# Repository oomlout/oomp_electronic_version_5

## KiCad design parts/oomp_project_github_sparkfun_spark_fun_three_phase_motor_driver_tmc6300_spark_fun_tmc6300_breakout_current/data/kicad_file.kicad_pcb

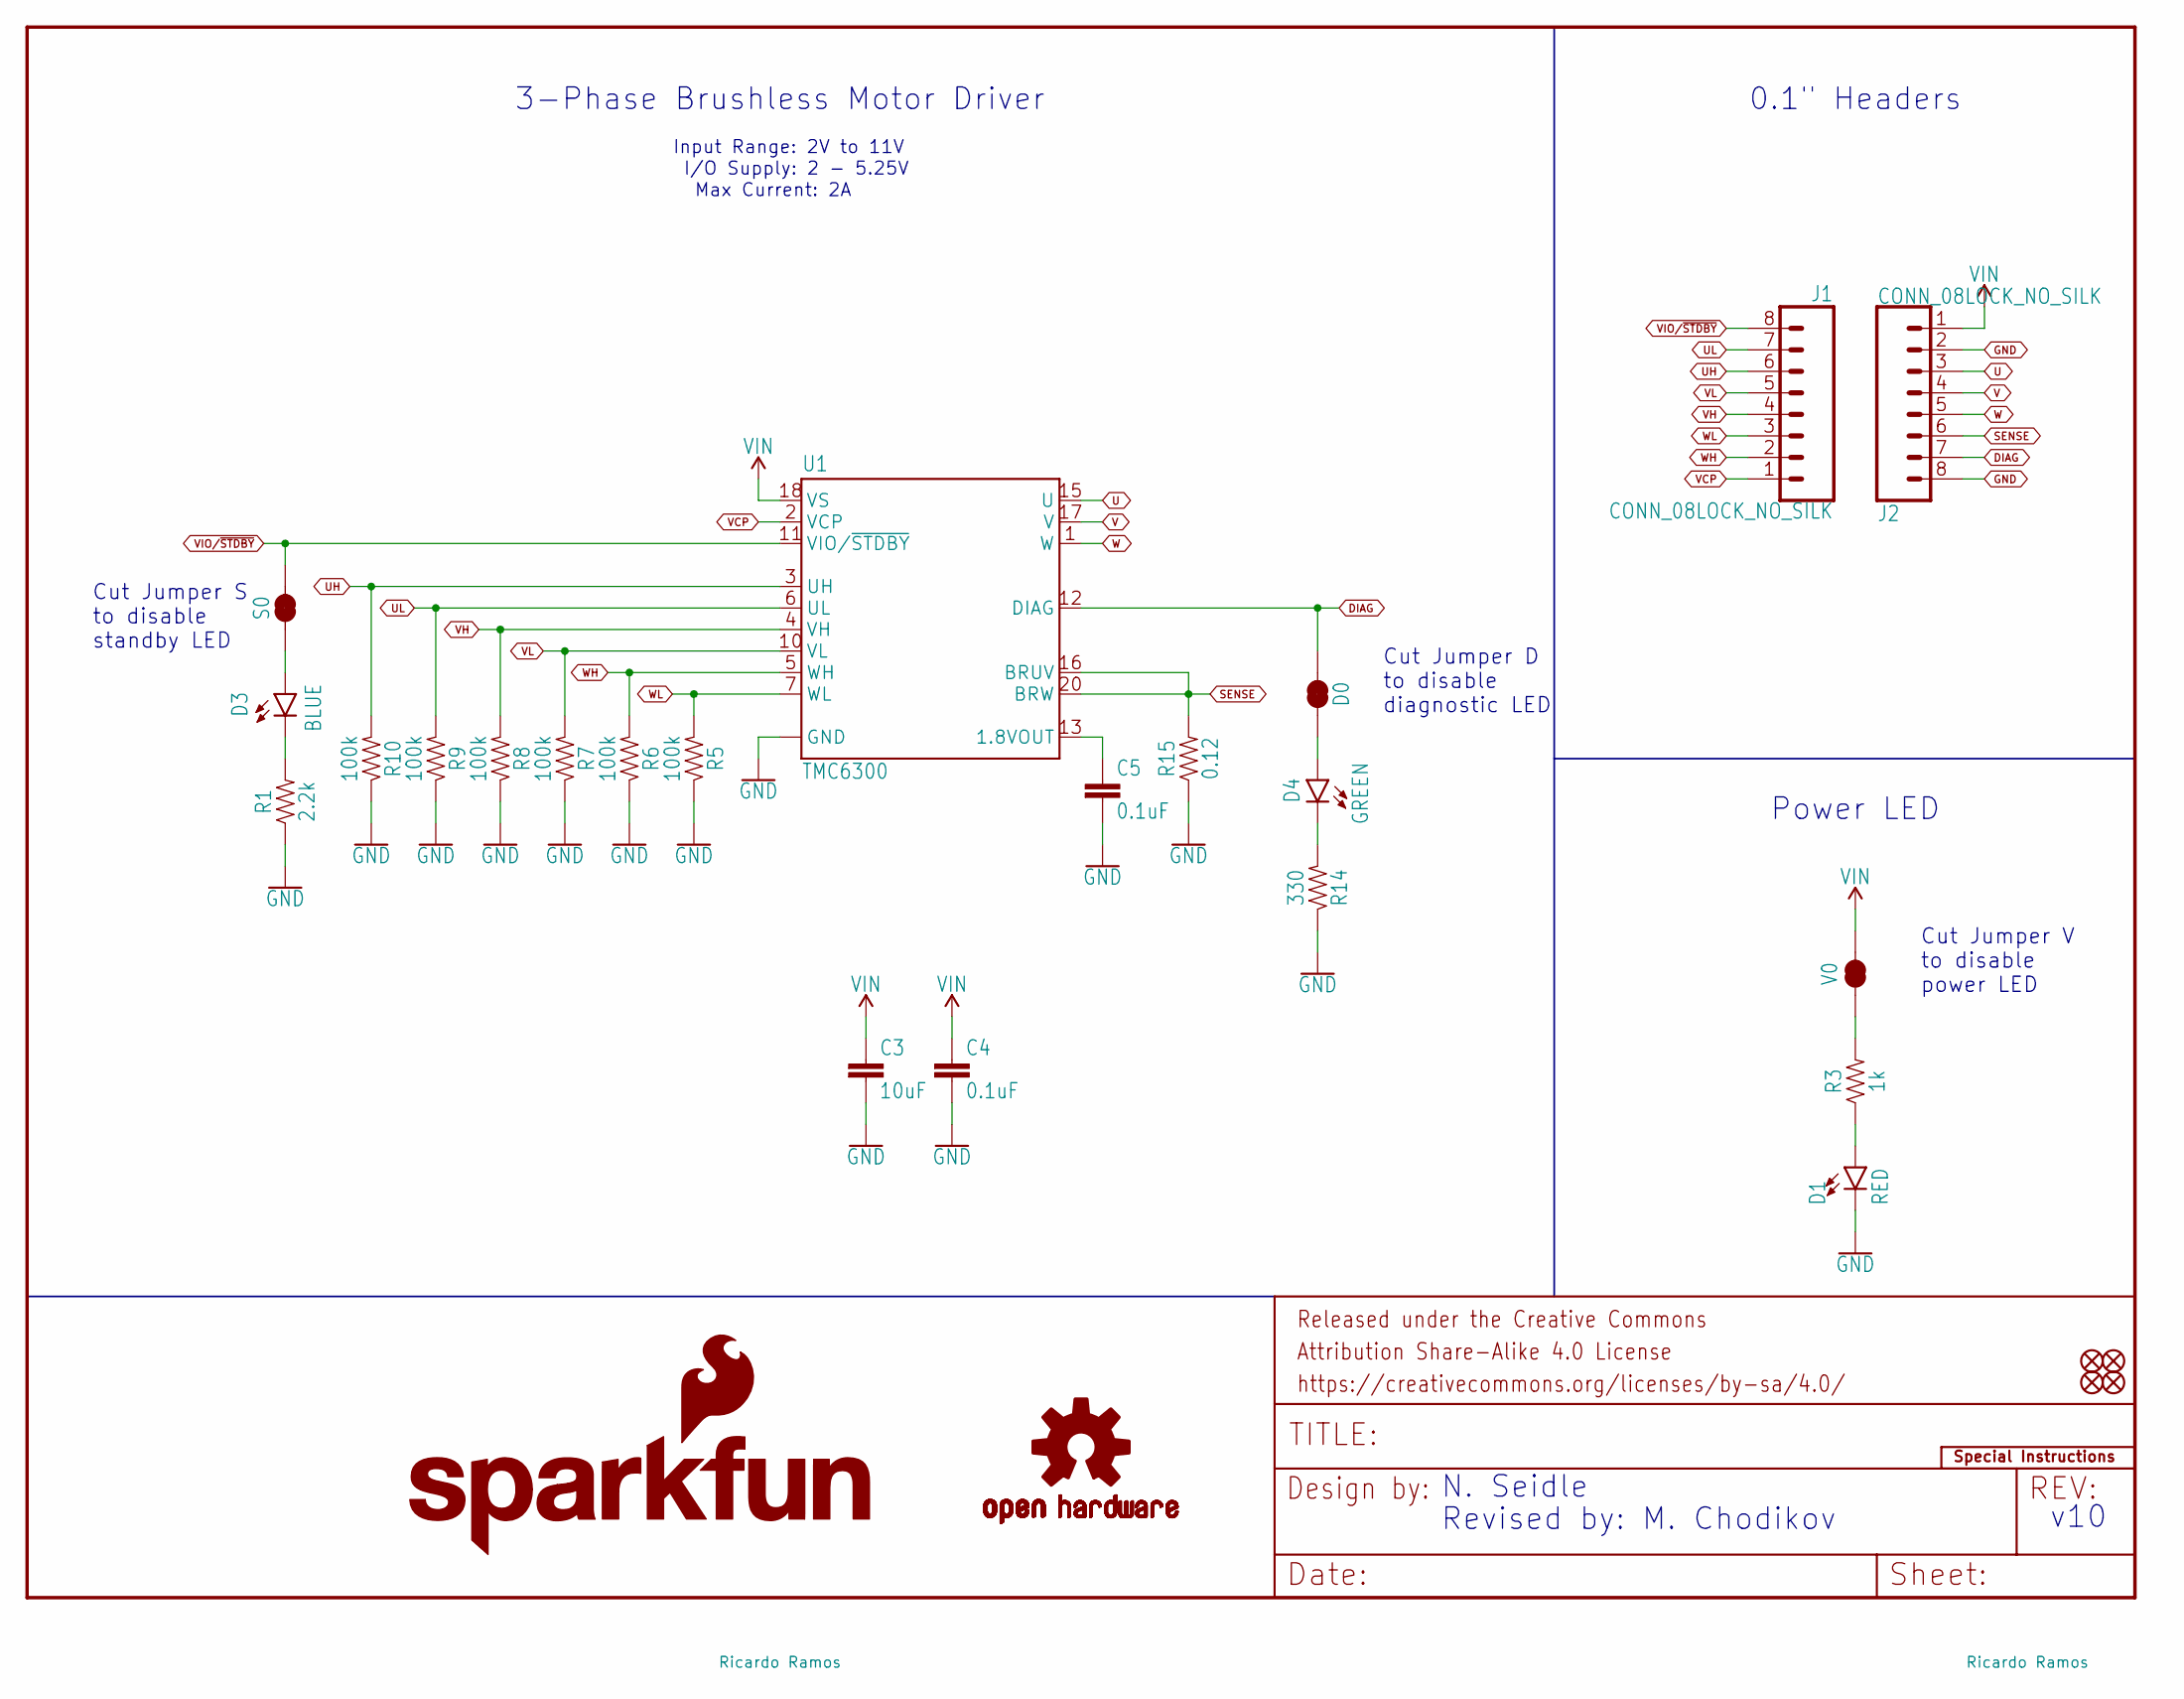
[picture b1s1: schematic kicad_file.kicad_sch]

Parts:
C3: 10uF; 0805
C4, C5: 0.1uF; 0603
D0: JUMPER-SMT_2_NC_TRACE_SILK; SMT-JUMPER_2_NC_TRACE_SILK
D1: RED; LED-0603
D3: BLUE; LED-0603
D4: GREEN; LED-0603
FD1, FD2, FD3, FD4: FIDUCIALUFIDUCIAL; FIDUCIAL-MICRO
FRAME1: FRAME-LETTER; CREATIVE_COMMONS
J1, J2: CONN_08LOCK_NO_SILK; 1X08_LOCK_NO_SILK
LOGO2: SPECIAL_INSTRUCTIONS-ORDERING; ORDERING_INSTRUCTIONS
LOGO3: SFE_LOGO_NAME.08_INCH; SFE_LOGO_NAME_.08
LOGO4: SFE_LOGO_FLAME.1_INCH; SFE_LOGO_FLAME_.1
LOGO5: OSHW-LOGOS; OSHW-LOGO-S
R1: 2.2k; 0603
R3: 1k; 0603
R5, R6, R7, R8, R9, R10: 100k; 0603
R14: 330; 0603
R15: 0.12; 1206
S0: JUMPER-SMT_2_NC_TRACE_SILK; SMT-JUMPER_2_NC_TRACE_SILK
U1: TMC6300; QFN-20
V0: JUMPER-SMT_2_NC_TRACE_SILK; SMT-JUMPER_2_NC_TRACE_SILK

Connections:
DIAG: D0.2, J2.7, U1.12 (DIAG)
GND: C3.2, C4.2, C5.2, D1.C, J2.2, J2.8, R1.1, R5.1, R6.1, R7.1, R8.1, R9.1, R10.1, R14.1, R15.1, U1.8 (GND), U1.9 (GND), U1.14 (GND), U1.PAD (GND)
unnamed: R3.2, V0.1
unnamed: D1.A, R3.1
unnamed: D3.A, S0.1
unnamed: C5.1, U1.13 (1.8VOUT)
unnamed: D0.1, D4.A
unnamed: D3.C, R1.2
unnamed: D4.C, R14.2
SENSE: J2.6, R15.2, U1.16 (BRUV), U1.20 (BRW)
U: J2.3, U1.15 (U)
UH: J1.6, R10.2, U1.3 (UH)
UL: J1.7, R9.2, U1.6 (UL)
V: J2.4, U1.17 (V)
VCP: J1.1, U1.2 (VCP)
VH: J1.4, R8.2, U1.4 (VH)
VIN: C3.1, C4.1, J2.1, U1.18 (VS), V0.2
VIO/~STDBY: J1.8, S0.2, U1.11 (VIO/~STDBY)
VL: J1.5, R7.2, U1.10 (VL)
W: J2.5, U1.1 (W)
WH: J1.2, R6.2, U1.5 (WH)
WL: J1.3, R5.2, U1.7 (WL)

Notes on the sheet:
v10
I/O Supply: 2 - 5.25V
N. Seidle
Power LED
Max Current: 2A
3-Phase Brushless Motor Driver
Input Range: 2V to 11V
Revised by: M. Chodikov
0.1" Headers
Cut Jumper V to disable power LED
Cut Jumper S to disable standby LED
Cut Jumper D to disable diagnostic LED

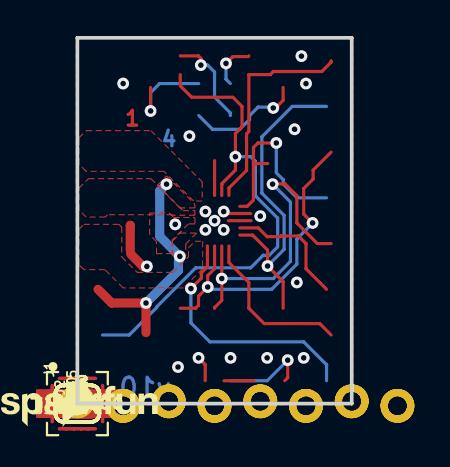
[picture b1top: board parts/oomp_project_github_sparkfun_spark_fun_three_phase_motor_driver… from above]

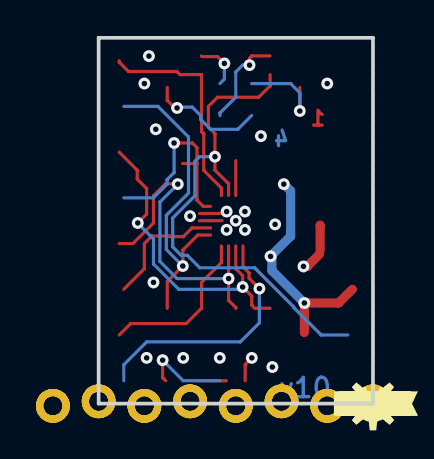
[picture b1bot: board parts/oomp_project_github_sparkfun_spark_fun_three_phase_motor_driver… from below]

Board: 4 copper layers, 15.2 x 20.3 mm, 56 parts (27 on the bottom side), 22 nets.

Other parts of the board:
U$1, U$28: #GND#1
U$2: #SEN#0
U$3: #DIAG#0
U$4: TMC630063003454
U$9: #U#6
U$12: #VCP#0
U$13: #VIO#1
U$15: 63001
U$16, U$18: D0
U$19, U$27: S1
U$20, U$26: V2
U$21: #UH#5
U$22: #UL#4
U$23: TMC0
U$24: #VIN#0
U$25: #V#7
U$30: #VH#2
U$31: #VL#3
U$32: #W#8
U$33: #WH#1
U$34: #WL#0

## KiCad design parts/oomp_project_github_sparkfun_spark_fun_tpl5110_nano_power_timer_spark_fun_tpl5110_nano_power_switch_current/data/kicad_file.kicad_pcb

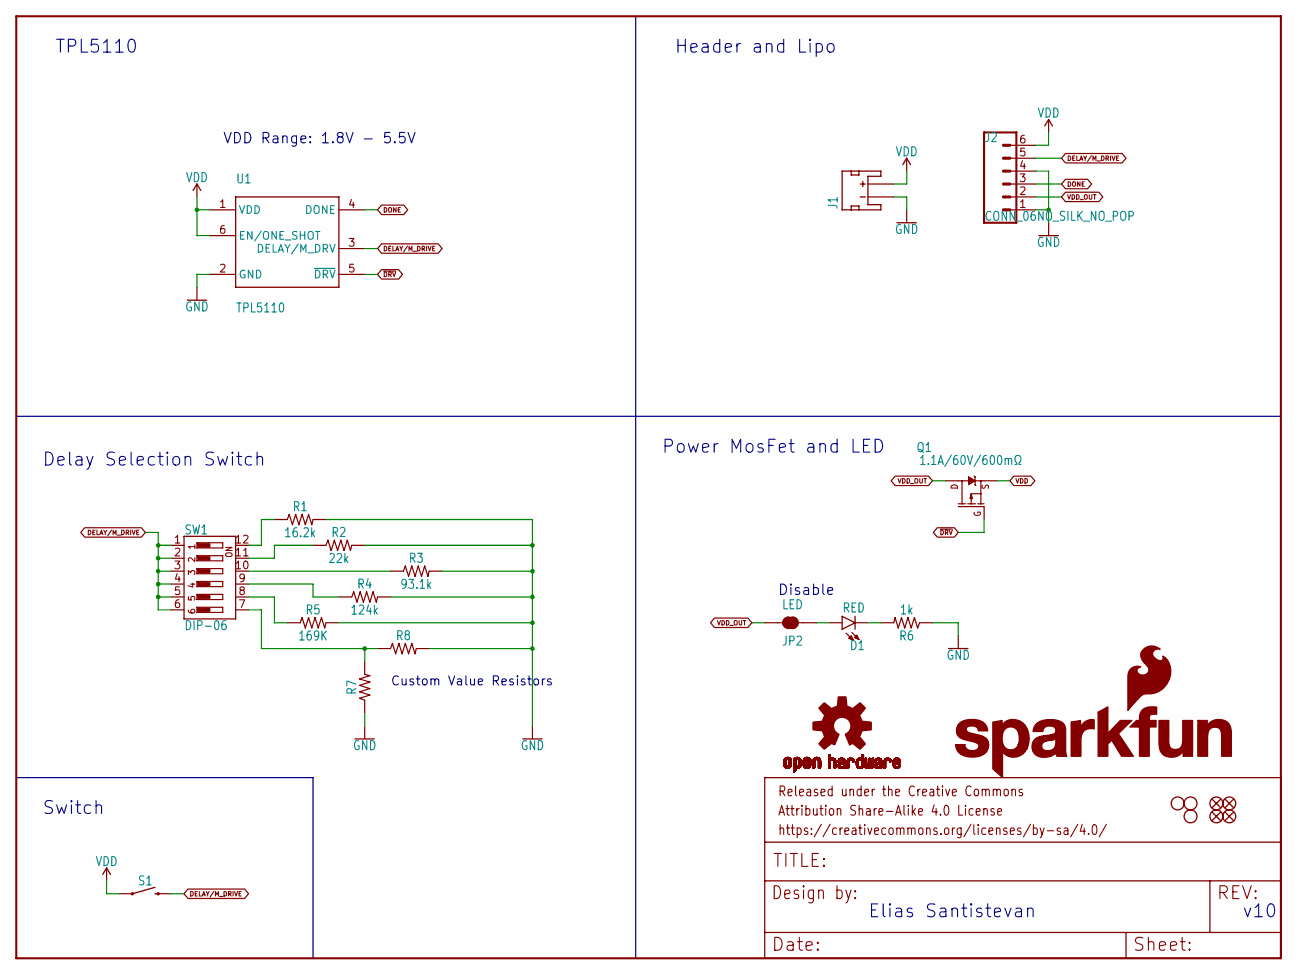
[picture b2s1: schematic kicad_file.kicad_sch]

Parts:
D1: RED; LED-0603
FD1, FD2, FD3, FD4: FIDUCIALUFIDUCIAL; FIDUCIAL-MICRO
FRAME1: FRAME-LETTER; CREATIVE_COMMONS
H1, H2, H4: STAND-OFFTIGHT; STAND-OFF-TIGHT
J1: JST_2MM_MALE; JST-2-SMD
J2: CONN_06NO_SILK_NO_POP; 1X06_NO_SILK
JP2: LED; SMT-JUMPER_2_NC_TRACE_SILK
LOGO1: SFE_LOGO_NAME.1_INCH; SFE_LOGO_NAME_.1
LOGO2: OSHW-LOGOS; OSHW-LOGO-S
LOGO3: SFE_LOGO_FLAME.1_INCH; SFE_LOGO_FLAME_.1
Q1: 1.1A/60V/600mΩ; SOT23-3
R1: 16.2k; 0603
R2: 22k; 0603
R3: 93.1k; 0603
R4: 124k; 0603
R5: 169K; 0603
R6: 1k; 0603
R7: 0603
R8: AXIAL-0.3
S1: MOMENTARY-SWITCH-SPST-SMD-5.2MM-TALL; TACTILE_SWITCH_SMD_5.2MM
SW1: DIP-06; DIPSWITCH-06-SMD
U1: TPL5110; SOT23-6

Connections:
DELAY/M_DRIVE: J2.5, S1.3 (2), SW1.1, SW1.2, SW1.3, SW1.4, SW1.5, SW1.6, U1.3 (DELAY/M_DRV)
DONE: J2.3, U1.4 (DONE)
GND: J1.1 (-), J2.1, J2.4, R1.2, R2.2, R3.2, R4.2, R5.2, R6.1, R7.1, R8.P$2 (2), U1.2 (GND)
unnamed: D1.C, R6.2
unnamed: R1.1, SW1.12
unnamed: R2.1, SW1.11
unnamed: R3.1, SW1.10
unnamed: R4.1, SW1.9
unnamed: R5.1, SW1.8
unnamed: R7.2, R8.P$1 (1), SW1.7
unnamed: D1.A, JP2.1
VDD: J1.2 (+), J2.6, Q1.2 (S), S1.1, U1.1 (VDD), U1.6 (EN/ONE_SHOT)
VDD_OUT: J2.2, JP2.2, Q1.3 (D)
~DRV: Q1.1 (G), U1.5 (~DRV)

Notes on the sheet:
Header and Lipo
Custom Value Resistors
Delay Selection Switch
Power MosFet and LED
Elias Santistevan
v10
TPL5110
Switch
VDD Range: 1.8V - 5.5V
Disable

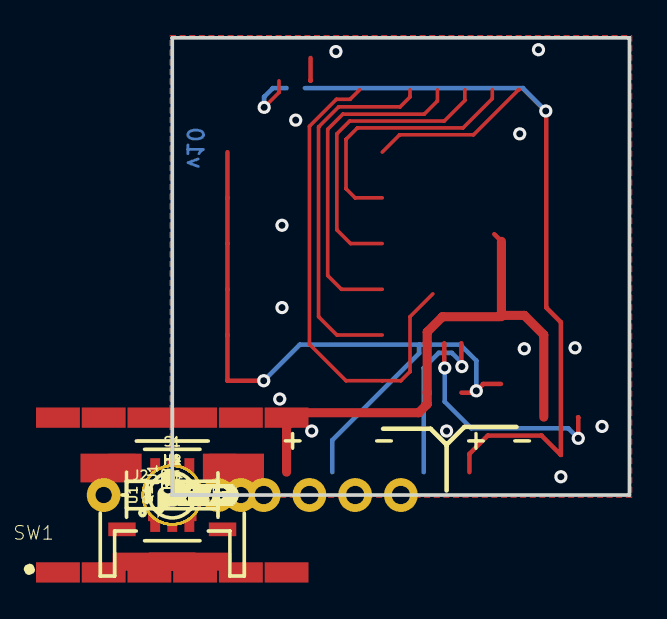
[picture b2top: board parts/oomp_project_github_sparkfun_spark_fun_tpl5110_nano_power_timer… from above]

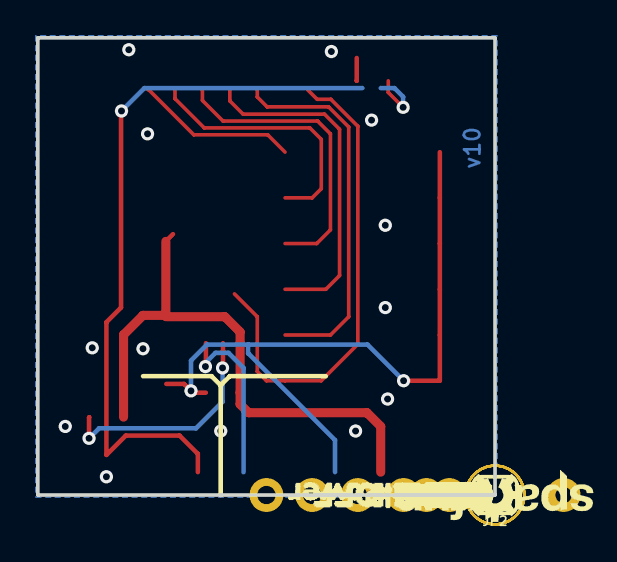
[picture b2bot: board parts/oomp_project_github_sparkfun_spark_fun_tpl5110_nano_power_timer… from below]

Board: 2 copper layers, 25.4 x 25.4 mm, 62 parts (29 on the bottom side), 14 nets.

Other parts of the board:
U$1: DONE0
U$2, U$4: GND-03
U$3: VOUT0
U$5: VDD0
U$6: NANO_POWER0
U$7: SWITCH0
U$8: 1M0
U$9: 30S4
U$10: 30M2
U$11: 1HR3
U$12: 2HR4
U$13: LED0
U$14: CUSTOM0
U$15: TIME#OFF0
U$16: DRV0
U$17, U$25: A0
U$18, U$26: B1
U$19, U$27: C2
U$20, U$28: D3
U$21, U$29: E4
U$22, U$23, U$24, U$30: F5
U$31, U$33: IN0
U$32, U$34: OUT1
U$35: PWR-()-03

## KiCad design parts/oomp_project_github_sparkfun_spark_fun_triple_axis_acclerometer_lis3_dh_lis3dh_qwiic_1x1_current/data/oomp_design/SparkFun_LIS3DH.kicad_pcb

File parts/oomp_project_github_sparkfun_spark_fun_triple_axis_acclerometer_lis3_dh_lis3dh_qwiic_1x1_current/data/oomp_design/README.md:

# OOMP KiCad design copy

Open `SparkFun_LIS3DH.kicad_pro` (or the `.kicad_pcb` / `.kicad_sch`) in KiCad. Local OOMP libraries are under `libraries/`. Original inputs are preserved in [../original/](../original/).

Only verified unchanged installed KiCad defaults were renamed. Modified, custom, unmatched and unavailable items remain unchanged. Soldering variants are never swapped during conversion. Existing pad coordinates, nets and UUIDs are preserved.

See [conversion_report.yaml](conversion_report.yaml) for every conversion and skip. Copy this directory before editing; regeneration refuses to overwrite edited design files.

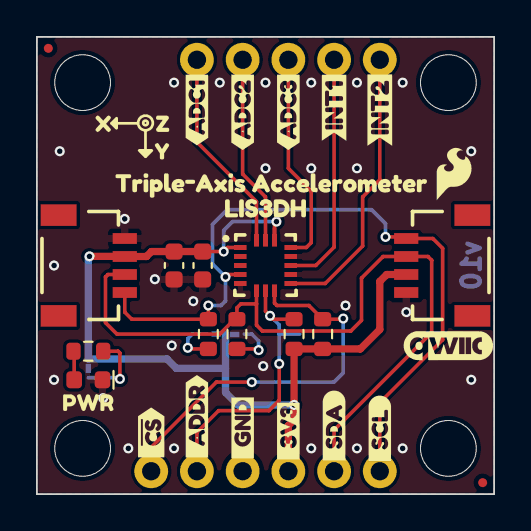
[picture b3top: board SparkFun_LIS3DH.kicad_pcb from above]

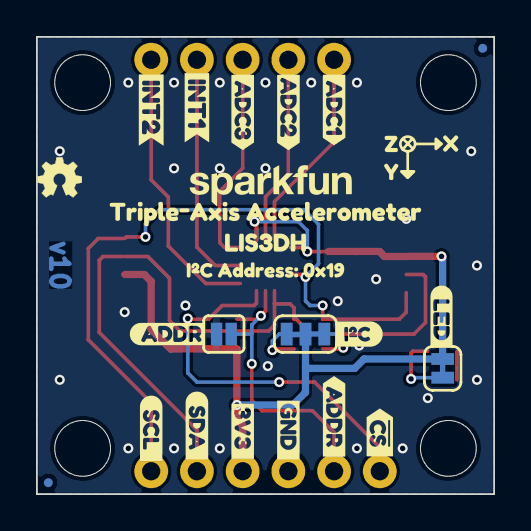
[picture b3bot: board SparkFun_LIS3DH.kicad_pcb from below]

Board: 2 copper layers, 25.4 x 25.4 mm, 64 parts (26 on the bottom side), 15 nets.

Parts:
C1: 10uF; C_0603_1608Metric
C2: 0.1uF; C_0603_1608Metric
D1: Red; LED_0603_1608Metric_Red
FID1, FID2, FID3, FID4: Fiducial_0.5mm; Fiducial_0.5mm_Mask1mm
G4: OSHW_Logo; Creative_Commons_License
J1: Conn_01x02; 1x02
J2: Conn_01x05; 1x05
J3, J5: Qwiic_RA; JST_SMD_1.0mm-4_Black
J4: I2C; 1x04
JP1: LED; Jumper_2_NC_Trace
JP2: I2C; Jumper_3_NC-2_Trace
JP3: ADDR; Jumper_2_NO
R1, R4: 10k; R_0603_1608Metric
R2, R3: 2.2k; R_0603_1608Metric
R5: 4.7k; R_0603_1608Metric
Ref**: Val**; OSHW_Logo_2.5mm
ST1, ST2, ST3, ST4: Standoff
U1: LIS3DH; ST_LGA-16_3x3mm_P0.5mm_5x3
kibuzzard-65A8A8B4: G***; kibuzzard-65A8A8B4
kibuzzard-67D9D97F: G***; kibuzzard-67D9D97F
kibuzzard-685C51A0, kibuzzard-685C51A0#2: G***; kibuzzard-685C51A0
kibuzzard-685C52CC, kibuzzard-685C52CC#2: G***; kibuzzard-685C52CC
kibuzzard-685C52E1, kibuzzard-685C52E1#2: G***; kibuzzard-685C52E1
kibuzzard-685C54A5: G***; kibuzzard-685C54A5
kibuzzard-685C54B5: G***; kibuzzard-685C54B5
kibuzzard-685C54BC: G***; kibuzzard-685C54BC
kibuzzard-685C549D: G***; kibuzzard-685C549D
kibuzzard-6838B6EB: G***; kibuzzard-6838B6EB
kibuzzard-6838B97C: G***; kibuzzard-6838B97C
kibuzzard-6838B744: G***; kibuzzard-6838B744
kibuzzard-6838B970: G***; kibuzzard-6838B970
kibuzzard-6838B976: G***; kibuzzard-6838B976
kibuzzard-6838B980: G***; kibuzzard-6838B980
kibuzzard-6838B984: G***; kibuzzard-6838B984
kibuzzard-6838B988: G***; kibuzzard-6838B988
kibuzzard-6838BA4A: G***; kibuzzard-6838BA4A
kibuzzard-6838BBAA: G***; kibuzzard-6838BBAA
kibuzzard-68376F48: G***; kibuzzard-68376F48
kibuzzard-68376F54: G***; kibuzzard-68376F54
kibuzzard-684892AC: G***; kibuzzard-684892AC
kibuzzard-684892BE: G***; kibuzzard-684892BE
kibuzzard-6837731A: G***; kibuzzard-6837731A
kibuzzard-6848928D: G***; kibuzzard-6848928D
kibuzzard-6848939E: G***; kibuzzard-6848939E
kibuzzard-68377305: G***; kibuzzard-68377305
kibuzzard-68377311: G***; kibuzzard-68377311
kibuzzard-68489282: G***; kibuzzard-68489282
kibuzzard-68489296: G***; kibuzzard-68489296
kibuzzard-68489323: G***; kibuzzard-68489323
kibuzzard-68489388: G***; kibuzzard-68489388
kibuzzard-68489408: G***; kibuzzard-68489408
kibuzzard-68489728: G***; kibuzzard-68489728

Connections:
3.3V: C1.1, C2.1, J3.2, J4.2, J5.2, JP1.2 (B), JP2.2 (B), R1.2, R4.2, U1.1 (VDDIO), U1.14 (VDD)
ADC1: J2.5, U1.16 (ADC1)
ADC2: J2.4, U1.15 (ADC2)
ADC3: J2.3, U1.13 (ADC3)
ADDR/SDO: J1.2, JP3.2 (B), R4.1, U1.7 (SA0/SDO)
GND: C1.2, C2.2, D1.1 (K), J3.1, J4.1, J5.1, JP3.1 (A), U1.5 (GND), U1.10 (RES), U1.12 (GND)
INT1: J2.2, U1.11 (INT1)
INT2: J2.1, U1.9 (INT2)
unnamed: D1.2 (A), R5.1
unnamed: JP1.1 (A), R5.2
unnamed: JP2.1 (A), R3.2
unnamed: JP2.3 (C), R2.2
SCL: J3.4, J4.4, J5.4, R3.1, U1.4 (SCL/SPC)
SDA: J3.3, J4.3, J5.3, R2.1, U1.6 (SDA/SDI)
~CS: J1.1, R1.1, U1.8 (~CS/MODE)

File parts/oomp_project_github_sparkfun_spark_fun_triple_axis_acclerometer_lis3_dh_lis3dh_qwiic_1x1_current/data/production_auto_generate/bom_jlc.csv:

Comment,Designator,Footprint,LCSC Part #
0.1uF,C2,SparkFun-Capacitor:C_0603_1608Metric,C14663
10k,"R1,R4",SparkFun-Resistor:R_0603_1608Metric,C98220
10uF,C1,SparkFun-Capacitor:C_0603_1608Metric,C19702
2.2k,"R2,R3",SparkFun-Resistor:R_0603_1608Metric,C4190
4.7k,R5,SparkFun-Resistor:R_0603_1608Metric,C23162
ADDR,JP3,SparkFun-Jumper:Jumper_2_NO,
Conn_01x02,J1,SparkFun-Connector:1x02,C492401
Conn_01x05,J2,SparkFun-Connector:1x05,C42431835
I2C,J4,SparkFun-Connector:1x04,C42431795
I2C,JP2,SparkFun-Jumper:Jumper_3_NC-2_Trace,
LED,JP1,SparkFun-Jumper:Jumper_2_NC_Trace,
LIS3DH,U1,SparkFun-Sensor:ST_LGA-16_3x3mm_P0.5mm_5x3,
Qwiic_RA,"J3,J5",SparkFun-Connector:JST_SMD_1.0mm-4_Black,C160404
Red,D1,SparkFun-LED:LED_0603_1608Metric_Red,

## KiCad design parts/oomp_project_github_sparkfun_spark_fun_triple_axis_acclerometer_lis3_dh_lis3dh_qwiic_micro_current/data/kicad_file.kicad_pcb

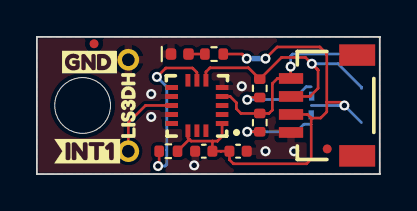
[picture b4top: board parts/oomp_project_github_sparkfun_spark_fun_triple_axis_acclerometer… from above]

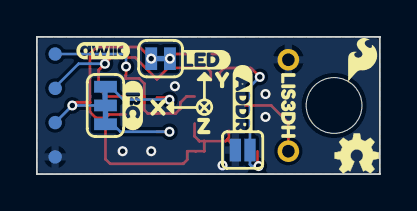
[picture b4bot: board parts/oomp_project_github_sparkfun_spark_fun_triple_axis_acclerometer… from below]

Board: 2 copper layers, 19.0 x 7.6 mm, 33 parts (15 on the bottom side), 10 nets.

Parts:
C3: 0.1uF; C_0402_1005Metric
C4: 10uF; C_0402_1005Metric
D1: Red; LED_0402_1005Metric_Red
FID3, FID4: Fiducial_0.5mm; Fiducial_0.5mm_Mask1mm
G4: OSHW_Logo; Creative_Commons_License
J1, J5: PTH_1x1mm; 1x01_1x1mm
J2: Qwiic_RA; JST_SMD_1.0mm-4_Black
JP1: LED; Jumper_2_NC_Trace
JP2: I2C; Jumper_3_NC-2_Trace
JP3: ADDR; Jumper_2_NO
R1, R6: 2.2k; R_0402_1005Metric
R2: 10k; R_0402_1005Metric
R3: 4.7k; R_0402_1005Metric
Ref**: Val**; OSHW_Logo_2.5mm
ST1: Standoff
TP5, TP6, TP7, TP8: 0.75mm; TestPoint-0.75mm
U1: LIS3DH; ST_LGA-16_3x3mm_P0.5mm_5x3
kibuzzard-685C51A0: G***; kibuzzard-685C51A0
kibuzzard-685C52CC: G***; kibuzzard-685C52CC
kibuzzard-685C52E1: G***; kibuzzard-685C52E1
kibuzzard-6841DC9E: G***; kibuzzard-6841DC9E
kibuzzard-6841DC10, kibuzzard-6841DC10#2: G***; kibuzzard-6841DC10
kibuzzard-6841DC42: G***; kibuzzard-6841DC42
kibuzzard-6841DC70: G***; kibuzzard-6841DC70
kibuzzard-68489829: G***; kibuzzard-68489829
kibuzzard-68489831: G***; kibuzzard-68489831

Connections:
3.3V: C3.1, C4.1, J2.2, JP1.2 (B), JP2.2 (B), R2.2, TP7.1, U1.1 (VDDIO), U1.14 (VDD)
ADDR/SDO: JP3.2 (B), R2.1, U1.7 (SA0/SDO)
GND: C3.2, C4.2, D1.1 (K), J2.1, J5.1, JP3.1 (A), TP8.1, U1.5 (GND), U1.10 (RES), U1.12 (GND)
INT1: J1.1, U1.11 (INT1)
unnamed: D1.2 (A), R3.2
unnamed: JP1.1 (A), R3.1
unnamed: JP2.1 (A), R6.2
unnamed: JP2.3 (C), R1.2
SCL: J2.4, R6.1, TP5.1, U1.4 (SCL/SPC)
SDA: J2.3, R1.1, TP6.1, U1.6 (SDA/SDI)

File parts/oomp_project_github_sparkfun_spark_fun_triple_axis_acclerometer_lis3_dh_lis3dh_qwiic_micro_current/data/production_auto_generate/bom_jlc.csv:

Comment,Designator,Footprint,LCSC Part #
0.1uF,C3,SparkFun-Capacitor:C_0402_1005Metric,C60474
0.75mm,"TP5,TP6,TP7,TP8",SparkFun-Connector:TestPoint-0.75mm,
10k,R2,SparkFun-Resistor:R_0402_1005Metric,C2906861
10uF,C4,SparkFun-Capacitor:C_0402_1005Metric,C15525
2.2k,"R1,R6",SparkFun-Resistor:R_0402_1005Metric,C2906920
4.7k,R3,SparkFun-Resistor:R_0402_1005Metric,C25900
ADDR,JP3,SparkFun-Jumper:Jumper_2_NO,
I2C,JP2,SparkFun-Jumper:Jumper_3_NC-2_Trace,
LED,JP1,SparkFun-Jumper:Jumper_2_NC_Trace,
LIS3DH,U1,SparkFun-Sensor:ST_LGA-16_3x3mm_P0.5mm_5x3,
PTH_1x1mm,"J1,J5",SparkFun-Connector:1x01_1x1mm,C7501259
Qwiic_RA,J2,SparkFun-Connector:JST_SMD_1.0mm-4_Black,C160404
Red,D1,SparkFun-LED:LED_0402_1005Metric_Red,

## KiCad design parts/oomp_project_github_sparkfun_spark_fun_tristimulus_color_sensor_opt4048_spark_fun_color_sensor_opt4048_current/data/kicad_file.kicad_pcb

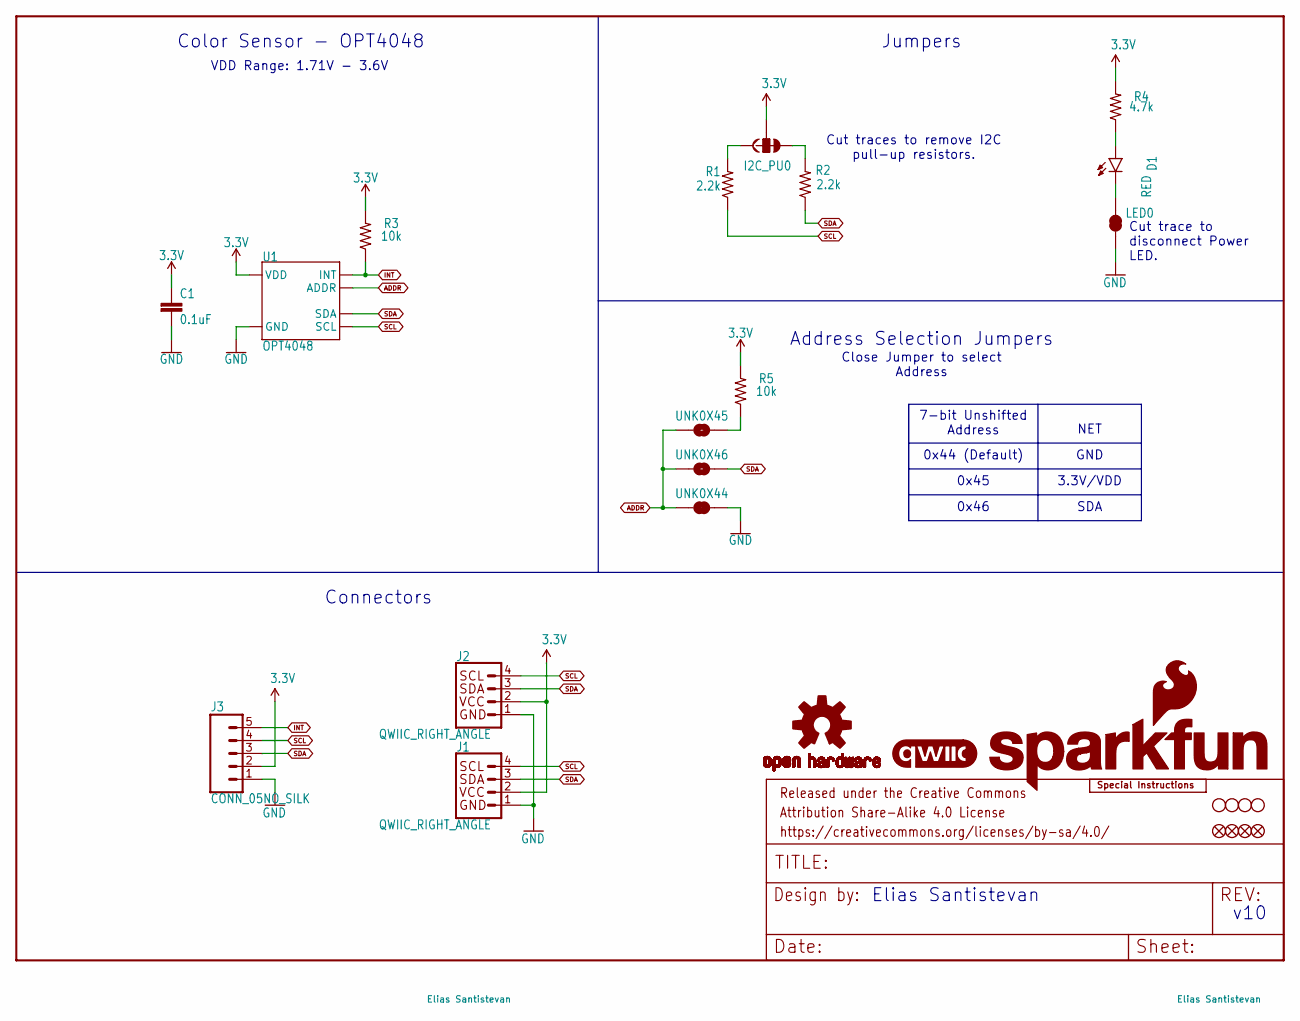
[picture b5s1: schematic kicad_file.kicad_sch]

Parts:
C1: 0.1uF; 0402-TIGHT
D1: RED; LED-0603
FD1, FD2: FIDUCIALUFIDUCIAL; FIDUCIAL-MICRO
FID1, FID2: FIDUCIALUFIDUCIAL; FIDUCIAL-MICRO
FRAME1: FRAME-LETTER; CREATIVE_COMMONS
I2C_PU0: S_MODE; SMT-JUMPER_3_2-NC_TRACE_SILK
J1, J2: QWIIC_RIGHT_ANGLE; JST04_1MM_RA
J3: CONN_05NO_SILK; 1X05_NO_SILK
LED0: JUMPER-SMT_2_NC_TRACE_SILK; SMT-JUMPER_2_NC_TRACE_SILK
LOGO1: QWIIC_LOGO_4MM; QWIIC_4MM
LOGO2: OSHW-LOGOMINI; OSHW-LOGO-MINI
LOGO3: SFE_LOGO_NAME_FLAME.1_INCH; SFE_LOGO_NAME_FLAME_.1
LOGO4: SPECIAL_INSTRUCTIONS-ORDERING; ORDERING_INSTRUCTIONS
R1, R2: 2.2k; 0603
R3, R5: 10k; 0603
R4: 4.7k; 0603
STANDOFF1, STANDOFF2, STANDOFF3, STANDOFF4: STAND-OFFTIGHT; STAND-OFF-TIGHT
U1: OPT4048; FCSOT
UNK0X44: JUMPER-SMT_2_NC_TRACE_SILK; SMT-JUMPER_2_NC_TRACE_SILK
UNK0X45, UNK0X46: JUMPER-SMT_2_NO_SILK; SMT-JUMPER_2_NO_SILK

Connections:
3.3V: C1.1, I2C_PU0.2, J1.2, J2.2, J3.2, R3.2, R4.2, R5.2, U1.P1 (VDD)
ADDR: U1.P2 (ADDR), UNK0X44.1, UNK0X45.1, UNK0X46.1
GND: C1.2, J1.1, J2.1, J3.1, LED0.1, U1.P4 (GND), UNK0X44.2
INT: J3.5, R3.1, U1.P7 (INT)
unnamed: D1.A, R4.1
unnamed: D1.C, LED0.2
unnamed: R5.1, UNK0X45.2
unnamed: I2C_PU0.1, R1.2
unnamed: I2C_PU0.3, R2.2
SCL: J1.4, J2.4, J3.4, R1.1, U1.P5 (SCL)
SDA: J1.3, J2.3, J3.3, R2.1, U1.P8 (SDA), UNK0X46.2

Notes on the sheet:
3.3V/VDD
Elias Santistevan
Cut traces to remove I2C pull-up resistors.
0x46
v10
Jumpers
Color Sensor - OPT4048
Connectors
GND
VDD Range: 1.71V - 3.6V
0x44 (Default)
Close Jumper to select Address
7-bit Unshifted Address
Address Selection Jumpers
0x45
NET
Cut trace to disconnect Power LED.
SDA

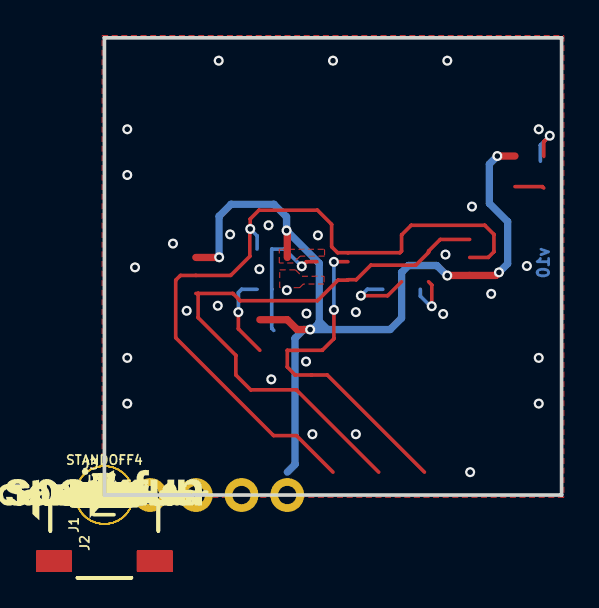
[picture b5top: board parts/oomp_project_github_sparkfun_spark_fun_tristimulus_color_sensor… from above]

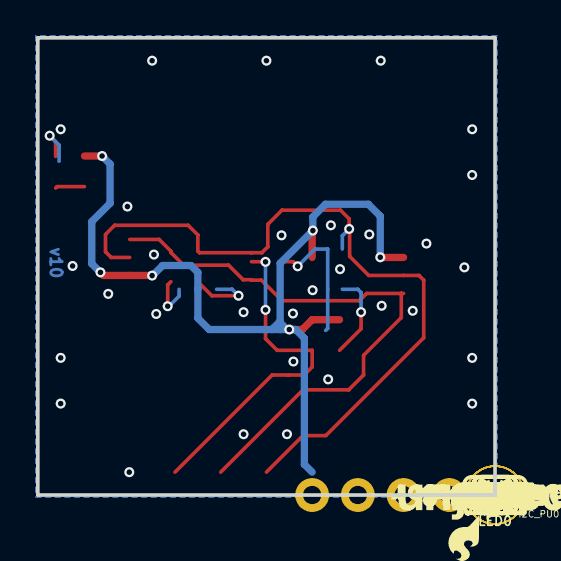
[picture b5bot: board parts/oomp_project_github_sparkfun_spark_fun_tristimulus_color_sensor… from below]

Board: 2 copper layers, 25.4 x 25.4 mm, 54 parts (22 on the bottom side), 11 nets.

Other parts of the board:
LOGO5: QWIIC_LOGO_4MM; QWIIC_4MM
U$1, U$15: #3V3#1
U$2, U$17: #GND#0
U$3: #SDA#1
U$4: #SDA#4
U$5, U$22: #SCL#5
U$6: #INT#3
U$7: #INT#9
U$8: #0X44#18
U$9, U$12: COLOR_SENSOR227
U$10: #I2C#227
U$11: #0X45#18
U$13: TRISTIMULUS228
U$14, U$19: OPT4048229
U$16: #LED#11
U$18: SFE_LOGO_NAME_.1
U$20: DEF_ADDRESS#_17
U$21: #0X46#18
U$28: PWR8
U$29: SFE_LOGO_FLAME_.1

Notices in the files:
parts/oomp_project_github_sparkfun_spark_fun_three_phase_motor_driver_tmc6300_spark_fun_tmc6300_breakout_current/data/original/kicad_file.kicad_sch:
Released under the Creative Commons
https://creativecommons.org/licenses/by-sa/4.0
parts and their libraries:
Released under the Creative Commons Attribution Share-Alike 4.0 License
